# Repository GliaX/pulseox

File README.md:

Pulse Oximeter
==============

This project aims to create a research-validated pulse oximeter whose plans are available freely and openly. The goal is for the device to cost under USD$25 to produce.

Currently, **THE PULSE OXIMETER IS NOT USABLE AND SHOULD NOT BE USED IN A CLINICAL SETTING.** The current version can be used for laboratory testing only.

Status
======
The device is undergoing clinical calibration as of 2019 OCTOBER 2.

Installation
============
Clone the repository and then do the following to initialize the submodules:

```
git submodule init
git submodule update
```

Licensing notes
===============
As per our understanding, hardware is not covered by copyright. However, we present
our work under the TAPR OHL license insofar as it applies. All software is covered by the GNU aGPL V3

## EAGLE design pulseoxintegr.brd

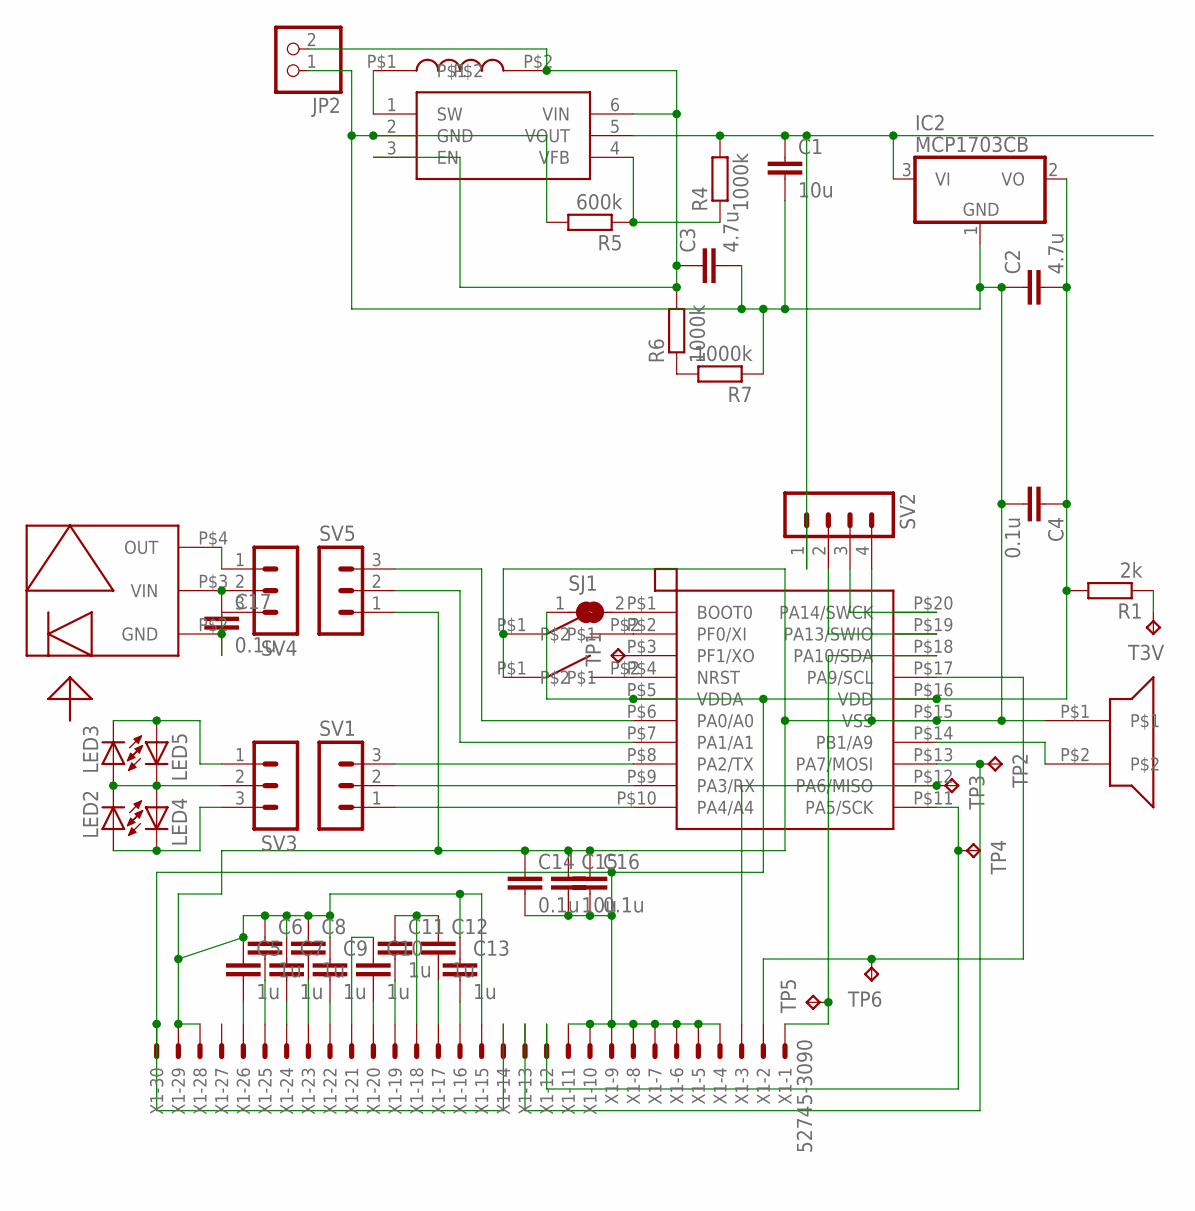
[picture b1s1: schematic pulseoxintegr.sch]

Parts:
C1, C15: 10u; C0603K
C2, C3: 4.7u; C0603K
C4, C14, C16, C17: 0.1u; C0603K
C5, C6, C7, C8, C9, C10, C11, C12, C13: 1u; C0603K
IC2: MCP1703CB; SOT23
JP2: PINHD-1X2; 1X02
LED2, LED3, LED4, LED5: LEDCHIP-LED0603; CHIP-LED0603
R1: 2k; R0603
R4, R6, R7: 1000k; R0603
R5: 600k; R0603
SJ1: SJ
SV1, SV3, SV4, SV5: MA03-1
SV2: MA04-1
T3V: TPTP11R; TP11R
TP1, TP2, TP3, TP4, TP5, TP6: TPTP11R; TP11R
U$1: TSL12T
U$2: MCP1640SOT23-6; SOT23-6L
U$3: WE-TPC
U$4: STM32F030F4P6; TSSOP-20
U$5, U$6: FSMSM
U$7: AT-2440-TWT-R
X1: 52745-3090

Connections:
3V: C2.2, C4.1, C14.2, C15.2, C16.2, IC2.2 (VO), R1.2, SJ1.1, U$4.P$5 (VDDA), U$4.P$16 (VDD), X1.4, X1.5, X1.6, X1.7, X1.8, X1.9, X1.10, X1.11, X1.14, X1.30
GND: C1.2, C2.1, C3.2, C4.2, C5.1, C6.1, C7.1, C8.1, C9.1, C13.1, C14.1, C15.1, C16.1, IC2.1 (GND), JP2.1, R5.2, R7.1, SV2.4, SV5.1, U$2.2 (GND), U$4.P$15 (VSS), U$5.P$1, U$6.P$1, U$7.P$1, X1.15, X1.28, X1.29
unnamed: SV5.3, U$4.P$6 (PA0/A0)
unnamed: SV5.2, U$4.P$7 (PA1/A1)
unnamed: U$4.P$14 (PB1/A9), U$7.P$2
unnamed: SV1.3, U$4.P$8 (PA2/TX)
unnamed: SV1.2, U$4.P$9 (PA3/RX)
unnamed: SV1.1, U$4.P$10 (PA4/A4)
unnamed: U$4.P$4 (NRST), U$5.P$2
unnamed: C1.1, IC2.3 (VI), R4.2, SV2.1, U$2.5 (VOUT)
unnamed: U$2.1 (SW), U$3.P$1
unnamed: R4.1, R5.1, U$2.4 (VFB)
unnamed: C3.1, JP2.2, R6.2, U$2.3 (EN), U$2.6 (VIN), U$3.P$2
unnamed: SV2.3, U$4.P$20 (PA14/SWCK)
unnamed: SV2.2, U$4.P$19 (PA13/SWIO)
unnamed: C17.1, SV4.2, U$1.P$3 (VIN)
unnamed: R6.1, R7.2
unnamed: C17.2, SV4.3, U$1.P$2 (GND)
unnamed: SV4.1, U$1.P$4 (OUT)
unnamed: C5.2, X1.26
unnamed: C6.2, X1.25
unnamed: C7.2, X1.24
unnamed: C8.2, X1.23
unnamed: C9.2, X1.22
unnamed: LED2.C, LED3.A, LED4.A, LED5.C, SV3.2
unnamed: LED2.A, LED4.C, SV3.3
unnamed: LED3.C, LED5.A, SV3.1
unnamed: C10.2, X1.20
unnamed: C12.2, X1.17
unnamed: C11.2, X1.19
unnamed: C13.2, X1.16
unnamed: C11.1, C12.1, X1.18
unnamed: C10.1, X1.21
unnamed: TP6.TP, U$4.P$17 (PA9/SCL), X1.2
unnamed: TP4.TP, U$4.P$11 (PA5/SCK), X1.12
unnamed: TP2.TP, U$4.P$13 (PA7/MOSI), X1.13
unnamed: TP3.TP, U$4.P$12 (PA6/MISO), X1.3
unnamed: TP5.TP, U$4.P$18 (PA10/SDA), X1.1
unnamed: U$4.P$2 (PF0/XI), U$6.P$2
unnamed: SJ1.2, U$4.P$1 (BOOT0)
unnamed: TP1.TP, U$4.P$3 (PF1/XO)
T3V: R1.1, T3V.TP

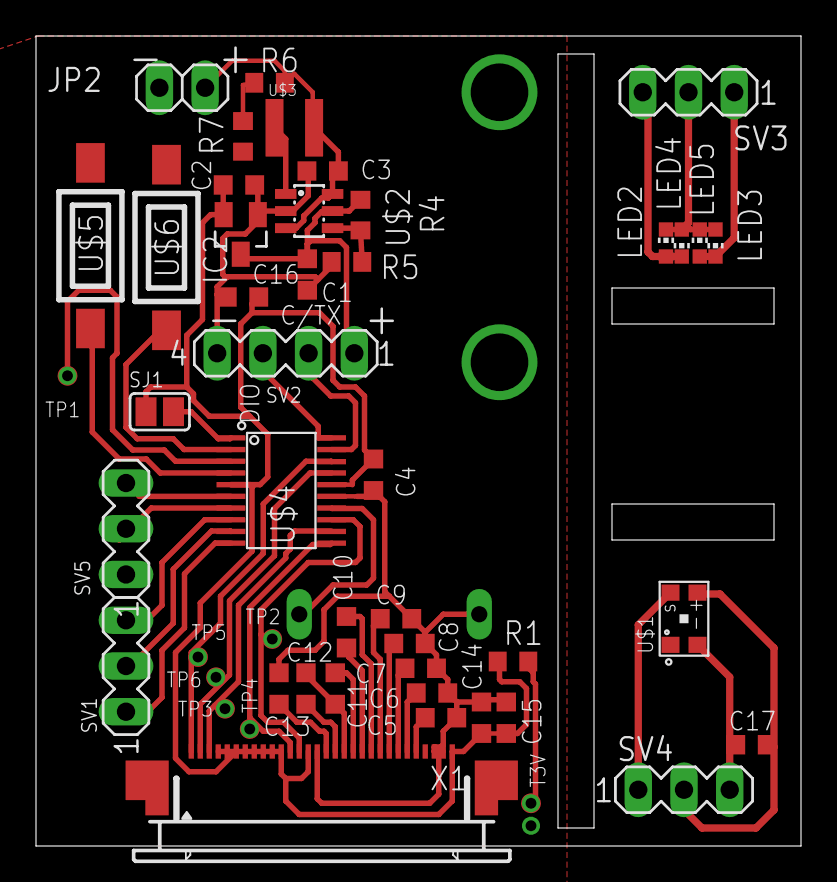
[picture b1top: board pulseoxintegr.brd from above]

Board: 2 copper layers, 42.5 x 45.0 mm, 49 parts (0 on the bottom side), 42 nets.

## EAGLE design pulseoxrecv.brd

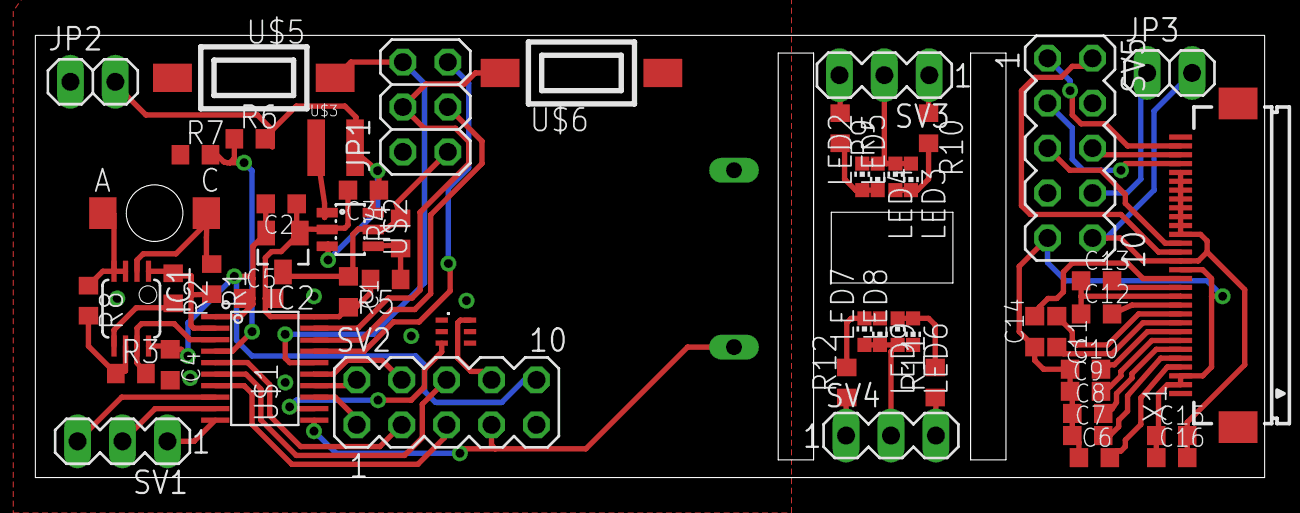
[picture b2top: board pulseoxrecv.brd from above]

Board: 2 copper layers, 69.5 x 25.0 mm, 55 parts (0 on the bottom side), 57 nets.

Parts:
C1, C16: 10u; C0603K
C2, C3: 4.7u; C0603K
C4, C5, C15: 0.1u; C0603K
C6, C7, C8, C9, C10, C11, C12, C13, C14: 1u; C0603K
IC1: LMV358MM; MSOP08
IC2: MCP1703CB; SOT23
JP1: 2X03
JP2, JP3: 1X02
LED1: QSB34ZR; R-PLCC2
LED2, LED3, LED4, LED5, LED6, LED7, LED8, LED9: CHIP-LED0603
R1: 60k; R0603
R2: 10k; R0603
R3: 29k; R0603
R4, R6, R7: 1000k; R0603
R5: 600k; R0603
R8, R9, R10, R11, R12: 1k; R0603
SV1, SV3, SV4: MA03-1
SV2, SV5: MA05-2
U$1: MSP430G2452IPW20; TSSOP-20
U$2: MCP1640SOT23-6; SOT23-6L
U$3: WE-TPC
U$4: BSD816SN; SOT363
U$5, U$6: FSMSM
U$7: AT-2440-TWT-R
X1: FH12-30S-0.5SH

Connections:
3V: C2.2, C4.1, C5.1, IC1.8, IC2.2, SV2.10, U$1.P$1
GND: C1.2, C2.1, C3.2, C4.2, C5.2, IC1.3, IC1.4, IC2.1, JP1.2, JP2.1, LED1.A, R5.2, R7.1, R8.1, SV2.9, U$1.P$20, U$2.2, U$4.P$4, U$5.P$2, U$6.P$2, U$7.P$2
unnamed: IC1.2, LED1.C, R1.1
unnamed: SV2.4, U$1.P$15
unnamed: IC1.1, R1.2, R2.1, U$1.P$2
unnamed: IC1.5, R2.2
unnamed: IC1.6, R3.1, R8.2
unnamed: IC1.7, R3.2, U$1.P$3
unnamed: SV2.2, U$1.P$14
unnamed: C1.1, IC2.3, JP1.1, R4.2, U$2.5
unnamed: U$2.1, U$3.P$1
unnamed: R4.1, R5.1, U$2.4
unnamed: C3.1, JP2.2, R6.2, U$2.3, U$2.6, U$3.P$2
unnamed: SV1.1, U$1.P$10
unnamed: SV1.2, U$1.P$9
unnamed: SV1.3, U$1.P$8
unnamed: R6.1, R7.2, U$1.P$4
unnamed: SV2.1, U$1.P$13
unnamed: U$1.P$12, U$4.P$3
unnamed: SV2.7, U$1.P$11, U$7.P$1
unnamed: SV2.3, U$1.P$5
unnamed: SV2.6, U$1.P$6
unnamed: SV2.5, U$1.P$7
unnamed: SV2.8, U$4.P$6
unnamed: LED2.C, LED3.A, LED4.A, LED5.C, SV3.2
unnamed: LED2.A, LED4.C, R9.2
unnamed: LED3.C, LED5.A, R10.2
unnamed: R9.1, SV3.3
unnamed: R10.1, SV3.1
unnamed: LED6.C, LED7.A, LED8.A, LED9.C, SV4.2
unnamed: LED7.C, LED9.A, R12.2
unnamed: LED6.A, LED8.C, R11.2
unnamed: JP1.4, U$1.P$19, U$6.P$1
unnamed: R11.1, SV4.3
unnamed: R12.1, SV4.1
unnamed: JP1.3, U$1.P$18
unnamed: JP1.5, U$1.P$17
unnamed: JP1.6, U$1.P$16, U$5.P$1
unnamed: SV5.5, X1.18
unnamed: C7.2, X1.5
unnamed: C9.2, X1.7
unnamed: C6.2, X1.4
unnamed: C8.2, X1.6
unnamed: C10.2, X1.8
unnamed: C6.1, C7.1, C8.1, C9.1, C10.1, C14.1, C15.1, C16.1, SV5.9, X1.2, X1.3, X1.15
unnamed: C11.2, X1.9
unnamed: C11.1, X1.10
unnamed: C12.2, X1.11
unnamed: C13.2, X1.13
unnamed: C12.1, C13.1, X1.12
unnamed: C14.2, X1.14
unnamed: C15.2, C16.2, JP3.2, SV5.10, X1.16, X1.19, X1.20, X1.21, X1.22, X1.23, X1.24, X1.25, X1.26
unnamed: SV5.2, X1.17
unnamed: SV5.1, X1.29
unnamed: SV5.6, X1.28
unnamed: SV5.3, X1.27
unnamed: JP3.1, SV5.8

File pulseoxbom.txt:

Partlist

Exported from pulseoxrecv.sch at 5/31/14 12:18 AM

EAGLE Version 6.5.0 Copyright (c) 1988-2013 CadSoft

Assembly variant: 

Part     Value            Device           Package        Library      Sheet

C1       10u              C-EUC0603K       C0603K         rcl          1
C2       4.7u             C-EUC0603K       C0603K         rcl          1
C3       4.7u             C-EUC0603K       C0603K         rcl          1
C4       0.1u             C-EUC0603K       C0603K         rcl          1
C5       0.1u             C-EUC0603K       C0603K         rcl          1
C6       1u               C-EUC0603K       C0603K         rcl          1
C7       1u               C-EUC0603K       C0603K         rcl          1
C8       1u               C-EUC0603K       C0603K         rcl          1
C9       1u               C-EUC0603K       C0603K         rcl          1
C10      1u               C-EUC0603K       C0603K         rcl          1
C11      1u               C-EUC0603K       C0603K         rcl          1
C12      1u               C-EUC0603K       C0603K         rcl          1
C13      1u               C-EUC0603K       C0603K         rcl          1
C14      1u               C-EUC0603K       C0603K         rcl          1
C15      0.1u             C-EUC0603K       C0603K         rcl          1
C16      10u              C-EUC0603K       C0603K         rcl          1
IC1      LMV358MM         LMV358MM         MSOP08         linear       1
IC2      MCP1703CB        MCP1703CB        SOT23          linear       1
JP1                       PINHD-2X3        2X03           pinhead      1
JP2                       PINHD-1X2        1X02           pinhead      1
JP3                       PINHD-1X2        1X02           pinhead      1
LED1     QSB34ZR          QSB34ZR          R-PLCC2        pulseoxparts 1
LED2                      LEDCHIP-LED0603  CHIP-LED0603   led          1
LED3                      LEDCHIP-LED0603  CHIP-LED0603   led          1
LED4                      LEDCHIP-LED0603  CHIP-LED0603   led          1
LED5                      LEDCHIP-LED0603  CHIP-LED0603   led          1
LED6                      LEDCHIP-LED0603  CHIP-LED0603   led          1
LED7                      LEDCHIP-LED0603  CHIP-LED0603   led          1
LED8                      LEDCHIP-LED0603  CHIP-LED0603   led          1
LED9                      LEDCHIP-LED0603  CHIP-LED0603   led          1
R1       60k              R-EU_R0603       R0603          rcl          1
R2       10k              R-EU_R0603       R0603          rcl          1
R3       29k              R-EU_R0603       R0603          rcl          1
R4       1000k            R-EU_R0603       R0603          rcl          1
R5       600k             R-EU_R0603       R0603          rcl          1
R6       1000k            R-EU_R0603       R0603          rcl          1
R7       1000k            R-EU_R0603       R0603          rcl          1
R8       1k               R-EU_R0603       R0603          rcl          1
R9       1k               R-EU_R0603       R0603          rcl          1
R10      1k               R-EU_R0603       R0603          rcl          1
R11      1k               R-EU_R0603       R0603          rcl          1
R12      1k               R-EU_R0603       R0603          rcl          1
SV1                       MA03-1           MA03-1         con-lstb     1
SV2                       MA05-2           MA05-2         con-lstb     1
SV3                       MA03-1           MA03-1         con-lstb     1
SV4                       MA03-1           MA03-1         con-lstb     1
SV5                       MA05-2           MA05-2         con-lstb     1
U$1      MSP430G2452IPW20 MSP430G2452IPW20 TSSOP-20       pulseoxparts 1
U$2      MCP1640SOT23-6   MCP1640SOT23-6   SOT23-6L       motiondet    1
U$3      WE-TPC           WE-TPC           WE-TPC         pulseoxparts 1
U$4      BSD816SN         BSD816SN         SOT363         untitled     1
U$5      FSMSM            FSMSM            FSMSM          untitled     1
U$6      FSMSM            FSMSM            FSMSM          untitled     1
U$7      AT-2440-TWT-R    AT-2440-TWT-R    AT-2440-TWT-R  pulseoxparts 1
X1       FH12-30S-0.5SH   FH12-30S-0.5SH   FH12-30S-0.5SH con-hirose   1

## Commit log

2014-05-31 Add BOM
2014-05-31 first version of @Kliment 's PCB
2014-06-06 Add design files
2014-06-12 Add Energia code
2014-06-27 Background Information and basic theory. Will add Kliments design later
2014-06-30 Volume Reccomendations of Call Buzzer
2014-06-30 A folder to keep current documentation
2014-07-07 Updated documentation, addition of appendix A,B and further elaboration on design
2014-07-14 Add stm32f0-based pulse ox with new receiver module
2014-07-14 Remove temporary file
2014-07-15 move a silkscreen layer off one of the inductor pads
2014-08-12 Create PulseOx Bom - 2014-08-12
    Up to date pulseOx bom from mouser
2014-08-12 Update PulseOx Bom - 2014-08-12
2015-06-13 first prototype of finger clamp
2015-06-13 made top part finger channel much wider
2015-06-13 Renamed files to be more easily usable.
2015-06-13 Changed Readme to be more reasonable. Added introduction and current status
2015-06-14 Update Naming Convention of Sources
2015-06-14 Add WIP firmware
2015-06-14 made the pcb cuts deeper
2015-06-14 Addition of Technical Papers for Pulse Ox, Updating of Naming Convention
2015-06-14 -Addition of source papers -Changing of Paper Naming Convention
2016-04-06 Add ethics application
2016-05-04 Add Ethics board recommendation and response for resubmission
2016-05-04 Cleaned up file names to make more sense. Removed PDFs and duplicates
2016-06-28 Updated ethics application - unsorted
2016-07-23 Fix file names
2016-07-23 Add volunteer question form and protocol for desaturation study
2016-08-04 Add publication draft with introduction and calibration methods
2017-03-14 Allow for toner transfer creation of board
2017-03-14 Change case to fit lower-case naming convention
2017-03-14 Add Supporting letter to ethics from Dr. Dukelow
2017-03-14 Move old version to archive directory
2017-03-14 Update Bill of Materials
2017-03-14 Update PCB images to V2 board design
2017-03-15 First complete draft of PCB for etching
2018-01-10 Add Health Canada application
2018-01-10 Add tracked letters and protocols for resubmit
2018-01-10 Update Appendix and add tracked version. Add Response letter to HC (Alex draft)
2018-01-10 Small points of clarification
2018-01-10 Version ready for sending to HC
2018-01-30 updated footnote as per Olivia's request
2018-02-13 Add new screening deficiency letter and date last one
2018-03-30 Add ITA Request draft
2018-04-19 Add gitignore to remove lockfiles from libreoffice
2018-04-19 Accept tracked changes
2018-07-21 Rename to more reasonable name
2018-07-25 Add Health canada files
2018-07-25 Add status report
2018-08-08 Add proper ITA application files
2018-08-08 Renamed pulseox boards
2018-08-09 Edit format and add Phase 1 & 2 Letter of Information
2018-10-04 Start renaming files so that we can build history
2018-10-04 Rename all files to correct dating
2018-10-04 Rename first generation
    This is the process of creating a history of files.
2018-10-08 Rename protocol
2018-10-08 Move over 2016-05-04 material
2018-10-08 Add information for 2016-06-08 revisions
2018-10-08 Move 2017-05-02 resubmission over and rename appropriately to gain history
2018-12-19 add pdf copy of approved ethics application
2019-06-25 Change to current version of pulse oximeter (IRNAS version) and create all parts as submodules
2019-06-25 Updated README to reflect current status of repo
2019-06-25 add OHL License
2019-06-25 Add licensing notes
2019-09-30 Update Recruitment Poster to reflect new pulse ox photo and 2-3hrs time
2019-10-02 Slight edits
2019-10-02 Instructions for submodules
2019-10-03 First draft of Discharge Instructions
2019-10-05 Add Case report form
2019-10-05 Update Case Report Form
2019-10-11 Add pretrial checklist
